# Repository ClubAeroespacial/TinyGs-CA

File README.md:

# Placa ESP32-C3 + SX1278 (LoRa 433 MHz) — Version2

Bring-up y validación de la revisión **Version2** de la placa.
Módulos: **ESP32-C3-WROOM-02-N4** (4 MB) + módulo **SX1278** de 433 MHz con conector u.FL.

**Estado: hardware validado.** 5 unidades fabricadas (3 + 2), todas funcionando.
Enlace LoRa bidireccional confirmado entre dos placas.

---

## Pinout

Verificado de dos formas independientes: extraído del netlist de KiCad
(`Version2.kicad_pcb`) y confirmado con firmware que corre en la placa.

| Señal | GPIO | Pad del módulo | Nota |
|---|---|---|---|
| LoRa SCK | **10** | 10 | |
| LoRa MISO | **6** | 5 | |
| LoRa MOSI | **7** | 6 | |
| LoRa NSS | **8** | 7 | strapping pin — ver ERRATA #4 |
| LoRa RESET | **5** | 4 | |
| LoRa DIO0 | **4** | 3 | conectado, permite usar interrupciones |
| UART TX | **21** | 12 | compartido con el LED — ver ERRATA #1 |
| UART RX | **20** | 11 | |
| Botón RESET | EN | 2 | |
| Botón BOOT | **0** | 18 | no es strapping pin — ver ERRATA #2 |
| Pull-up 10k (R10) | 2 | 16 | strapping, correcto |
| Pull-up 10k (R11) | 8 | 7 | strapping, correcto |

**GPIO libres:** 1, 3, 9, 18, 19
**DIO1–DIO5 del SX1278:** sin conectar

```cpp
#define PIN_SCK   10
#define PIN_MISO   6
#define PIN_MOSI   7
#define PIN_NSS    8
#define PIN_RST    5
#define PIN_DIO0   4
```

---

## Estado de validación

| Qué | Estado | Evidencia |
|---|---|---|
| Regulador 3.3 V (AMS1117) | OK | 3.3 V medidos, sin cortos |
| Arranque del ESP32-C3 | OK | mensaje de la ROM en UART |
| Flash 4 MB | OK | `flash-id` y sketches corriendo |
| UART bidireccional | OK | consola + flasheo exitoso |
| Modo programación | OK | `boot:0x5 (DOWNLOAD(USB/UART0/1))` |
| WiFi + estabilidad de fuente | OK | 6 redes, sin brownout en el pico de ~350 mA |
| SPI hacia el SX1278 | OK | `RegVersion = 0x12` estable |
| **Enlace LoRa bidireccional** | **OK** | PING/PONG entre 2 placas y test 14 del banco |
| **Test de producción completo** | **OK** | **14/14** en las unidades probadas |

Valores de referencia de placa sana: WiFi **-48 a -51 dBm** con 10-14 redes,
piso de ruido LoRa **-123 dBm**, frecuencia por defecto **434.0 MHz**.
Ver la tabla completa en [ERRATA.md](ERRATA.md).

### Todavía sin validar

- Alcance real (requiere antenas u.FL → SMA, aún no disponibles)
- Consumo en régimen y a batería
- Comportamiento térmico bajo carga sostenida

> **Nota sobre el -124 dBm:** la sensibilidad del SX1278 en SF7/BW125 es -123 dBm.
> El enlace funcionó **en el límite físico del chip**, sin antena y a 2 dBm, con
> ~8% de paquetes exitosos. Eso no es una falla: es el resultado esperado con los
> conectores u.FL al aire. Con antenas se espera -40 a -50 dBm a corta distancia.

---

## Cómo flashear

El programador usado es un **PL2303 sin DTR/RTS**, así que el modo descarga se
entra a mano.

### Cableado (TX y RX van cruzados)

```
PL2303              J2
------              --------------
GND     --------->  GND   (pin 1)
+5V     --------->  5V    (pin 2)
RXD     <---------  TX    (pin 3)
TXD     --------->  RX    (pin 4)
(nada)              RST   (pin 5)
(nada)              DTR   (pin 6)
```

### Configuración de Arduino IDE

| Opción | Valor |
|---|---|
| Board | ESP32C3 Dev Module |
| **USB CDC On Boot** | **Disabled** |
| Flash Mode | DIO |
| Flash Size | 4MB (32Mb) |
| Upload Speed | 921600 (probado y estable) |

### Secuencia

```
1. Mantener BOOT apretado
2. Apretar y soltar RESET
3. Soltar BOOT
4. Verificar en el monitor: boot:0x... (DOWNLOAD(USB/UART0/1))
5. Cerrar el Monitor Serie
6. Upload
7. Apretar RESET a mano (no hay RTS conectado)
```

**Indicador infalible:** el `boot:0x...` del mensaje de arranque.
`DOWNLOAD` = listo para flashear. `SPI_FAST_FLASH_BOOT` = no entraste.

---

## Sketches

| Carpeta | Qué prueba | Cuándo usarlo |
|---|---|---|
| `00_test_produccion/` | **14 pruebas automáticas con veredicto APROBADA / RECHAZADA** y línea CSV para planilla | **El de todos los días.** Es el banco de pruebas del lote. Ver la calibración de umbrales en ERRATA.md antes de correr una tanda |
| `04_test_lucas/` | Lee `RegVersion` del SX1278 por SPI | Primer test de una placa nueva si querés algo mínimo. 70 líneas, sin librerías |
| `01_smoke_test/` | CPU, flash, UART, LED, escaneo de WiFi | Validación general. El escaneo de WiFi es el que fuerza el pico de 350 mA y detecta problemas de fuente |
| `05_buscar_led/` | Versión corta del anterior | Cuando solo querés el estrés de fuente sin todo lo demás |
| `02_scan_sx1278/` | Encuentra los pines SPI por fuerza bruta | Si alguna vez hay una revisión nueva y no se conoce el pinout. Con el comando `v` verifica un pinout conocido en 2 segundos |
| `03_lora_pingpong/` | **Enlace de radio real entre 2 placas** | El único test que valida el amplificador, el cristal y el camino de antena |

> `04_test_lucas.ino` está **sin modificar**, tal como fue escrito originalmente.
> Se conserva así a propósito: es la referencia contra la que se comparó todo lo demás.

### Ping-pong: cómo se corre

El **mismo sketch** va en las dos placas. Las dos arrancan como RESPONDEDOR.
En la que tiene consola se manda `a` y pasa a EMISOR.

```
a  -> pasar a EMISOR        s  -> estadísticas
b  -> pasar a RESPONDEDOR   r  -> medir piso de ruido
t<n> -> potencia TX (2-17)  f<n> -> spreading factor (7-12)
d  -> cazar el pin DIO0
```

**Sin antena: 2 dBm y las placas a 5-10 cm.** No subir la potencia: el PA se
degrada transmitiendo contra un circuito abierto, y la degradación es silenciosa.

---

## Documentos

- **[ERRATA.md](ERRATA.md)** — los 7 defectos encontrados y qué cambiar en la v2
- **[00_GUIA_BRINGUP.md](00_GUIA_BRINGUP.md)** — guía completa de bring-up con mediciones
- **[PASOS_TEST_LUCAS.md](PASOS_TEST_LUCAS.md)** — procedimiento paso a paso con hitos

---

## Pendientes

- [ ] Comprar pigtails u.FL → SMA y antenas de 433 MHz (×5)
- [ ] Medir alcance real al aire libre
- [ ] Adaptador USB-TTL con DTR/RTS (CP2102 o CH340) para reset automático
- [ ] Regenerar los gerbers desde Version2 — ver ERRATA #7
- [ ] Aplicar los cambios de ERRATA.md a la v3

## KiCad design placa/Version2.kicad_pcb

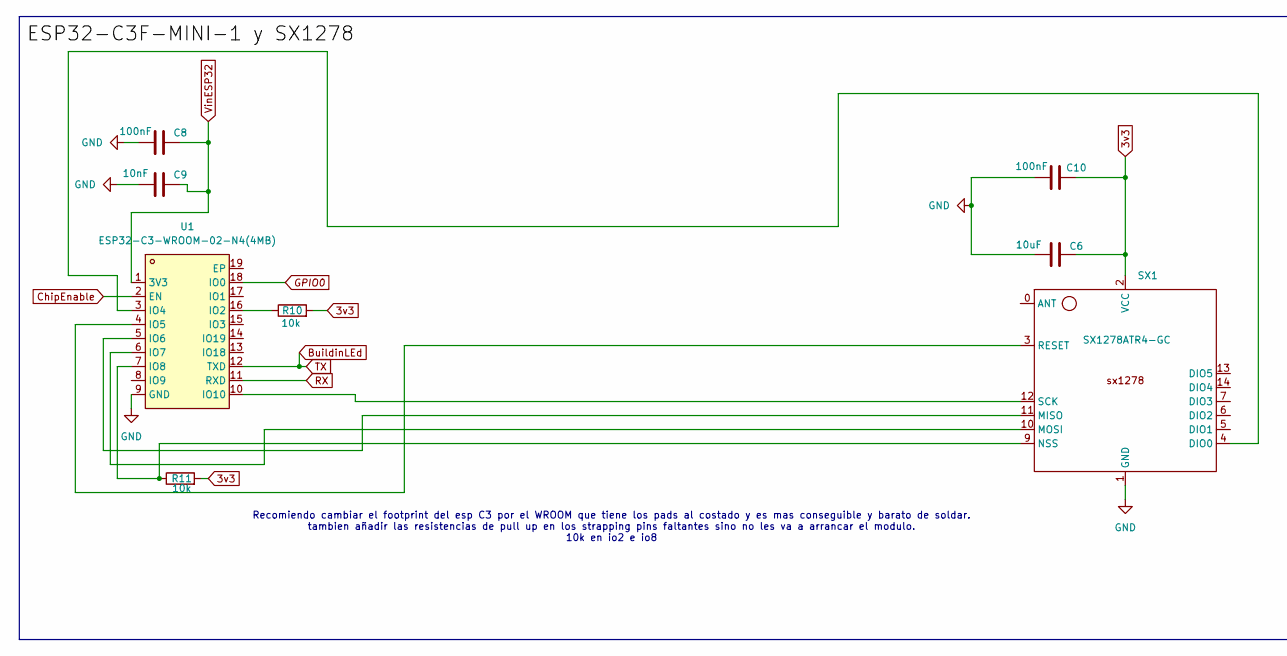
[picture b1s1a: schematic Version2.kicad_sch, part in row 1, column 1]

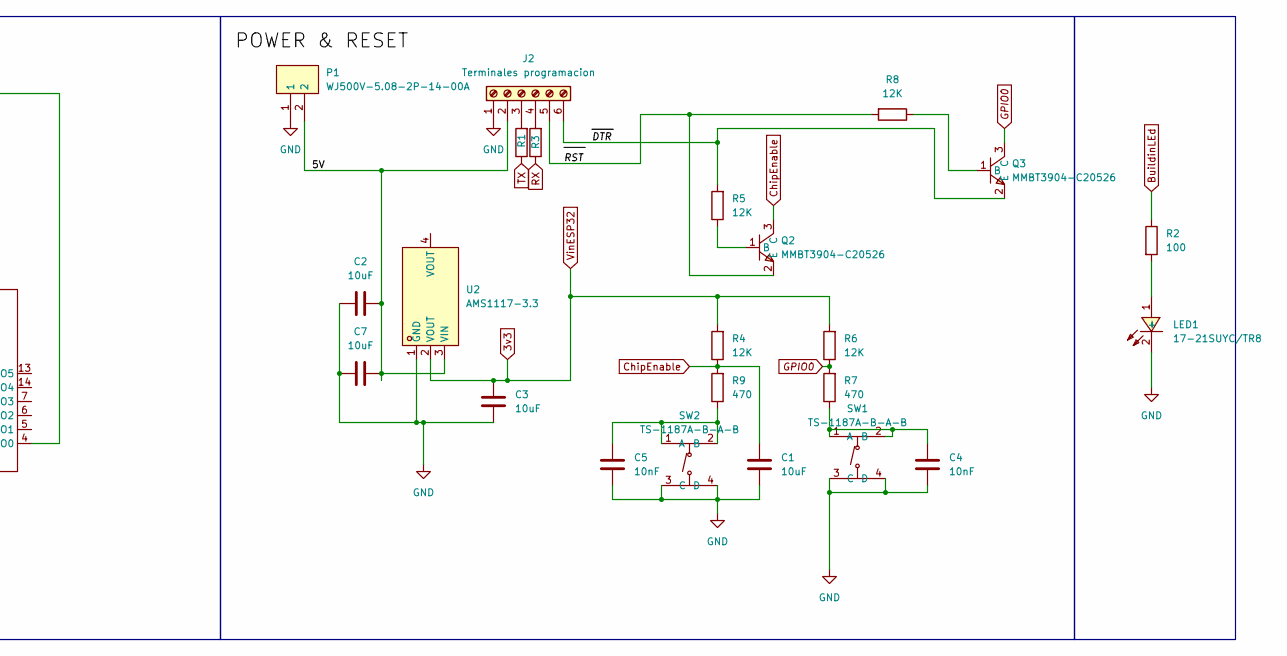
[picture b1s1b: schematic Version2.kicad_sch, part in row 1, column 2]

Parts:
C1, C2, C3, C6, C7: 10uF; C_0805_2012Metric
C4, C5, C9: 10nF; C_0402_1005Metric
C8, C10: 100nF; C_0402_1005Metric
J2: Terminales programacion; PinHeader_1x06_P2.54mm_Vertical; LCSC part C42431807
LED1: 17-21SUYC/TR8; LED_0805_2012Metric; LCSC Part C2296
P1: WJ500V-5.08-2P-14-00A; CONN-TH_2P-P5.00_WJ500V-5.08-2P; LCSC Part C8465
Q2, Q3: MMBT3904-C20526; SOT-23-3_L2.9-W1.3-P1.90-LS2.4-BR; LCSC Part C20526
R1, R3: 10; R_0603_1608Metric
R2: 100; R_0603_1608Metric
R4, R5, R6, R8: 12K; R_0603_1608Metric
R7, R9: 470; R_0603_1608Metric
R10, R11: 10k; R_0603_1608Metric; LCSC Part C31850
SW1, SW2: TS-1187A-B-A-B; SW-SMD_4P-L5.1-W5.1-P3.70-LS6.5-TL_H1.5; LCSC Part C318884
SX1: SX1278ATR4-GC; Sin título; LCSC part C42381680
U1: ESP32-C3-WROOM-02-N4(4MB); BULETM-SMD_ESPRESSIF_ESP32-C3-WROOM-02-N4-4MB; LCSC Part C2934560
U2: AMS1117-3.3; SOT-223-3_L6.5-W3.4-P2.30-LS7.0-BR; LCSC Part C6186

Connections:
3v3: C3.2, C6.2, C8.2, C9.2, C10.2, R4.2, R6.2, R10.2, R11.2, SX1.2 (VCC), U1.1 (3V3), U2.2 (VOUT)
/5V: C2.2, C7.2, J2.2, P1.2, U2.3 (VIN)
/DTR: J2.6, Q3.2 (E), R5.2
/RST: J2.5, Q2.2 (E), R8.2
BuildinLEd: R1.1, R2.1, U1.12 (TXD)
ChipEnable: C1.1, Q2.3 (C), R4.1, R9.2, U1.2 (EN)
GND: C1.2, C2.1, C3.1, C4.2, C5.2, C6.1, C7.1, C8.1, C9.1, C10.1, J2.1, LED1.2 (-), P1.1, SW1.3 (C), SW1.4 (D), SW2.3 (C), SW2.4 (D), SX1.1 (GND), U1.9 (GND), U2.1 (GND)
GPIO0: Q3.3 (C), R6.1, R7.2, U1.18 (IO0)
unnamed: J2.3, R1.2
unnamed: J2.4, R3.2
unnamed: LED1.1 (+), R2.2
unnamed: Q2.1 (B), R5.1
unnamed: Q3.1 (B), R8.1
unnamed: C4.1, R7.1, SW1.1 (A), SW1.2 (B)
unnamed: C5.1, R9.1, SW2.1 (A), SW2.2 (B)
unnamed: SX1.4 (DIO0), U1.3 (IO4)
unnamed: SX1.11 (MISO), U1.5 (IO6)
unnamed: SX1.10 (MOSI), U1.6 (IO7)
unnamed: R11.1, SX1.9 (NSS), U1.7 (IO8)
unnamed: SX1.3 (RESET), U1.4 (IO5)
unnamed: SX1.12 (SCK), U1.10 (IO10)
unnamed: R10.1, U1.16 (IO2)
RX: R3.1, U1.11 (RXD)

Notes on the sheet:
Recomiendo cambiar el footprint del esp C3 por el WROOM que tiene los pads al costado y es mas conseguible y barato de soldar. tambien añadir las resistencias de pull up en los strapping pins faltantes sino no les va a arrancar el modulo. 10k en io2 e io8

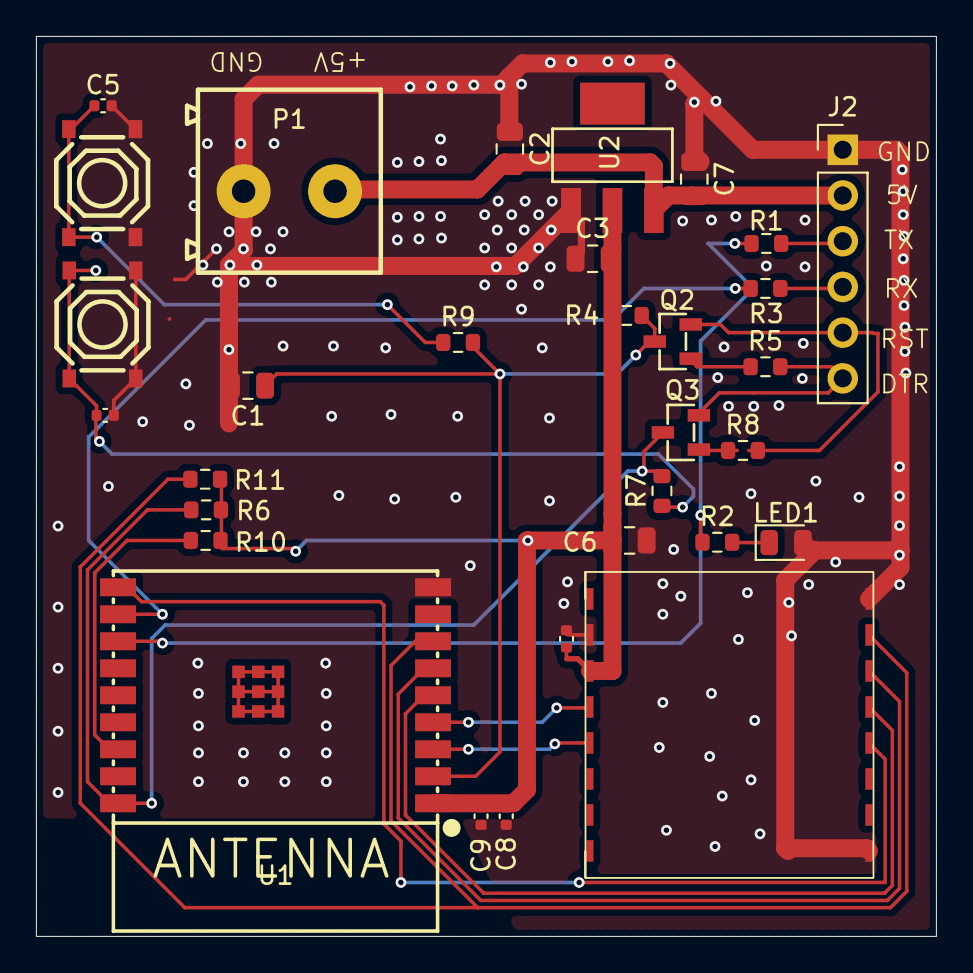
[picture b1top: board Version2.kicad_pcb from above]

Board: 2 copper layers, 50.0 x 50.0 mm, 31 parts (0 on the bottom side), 23 nets.

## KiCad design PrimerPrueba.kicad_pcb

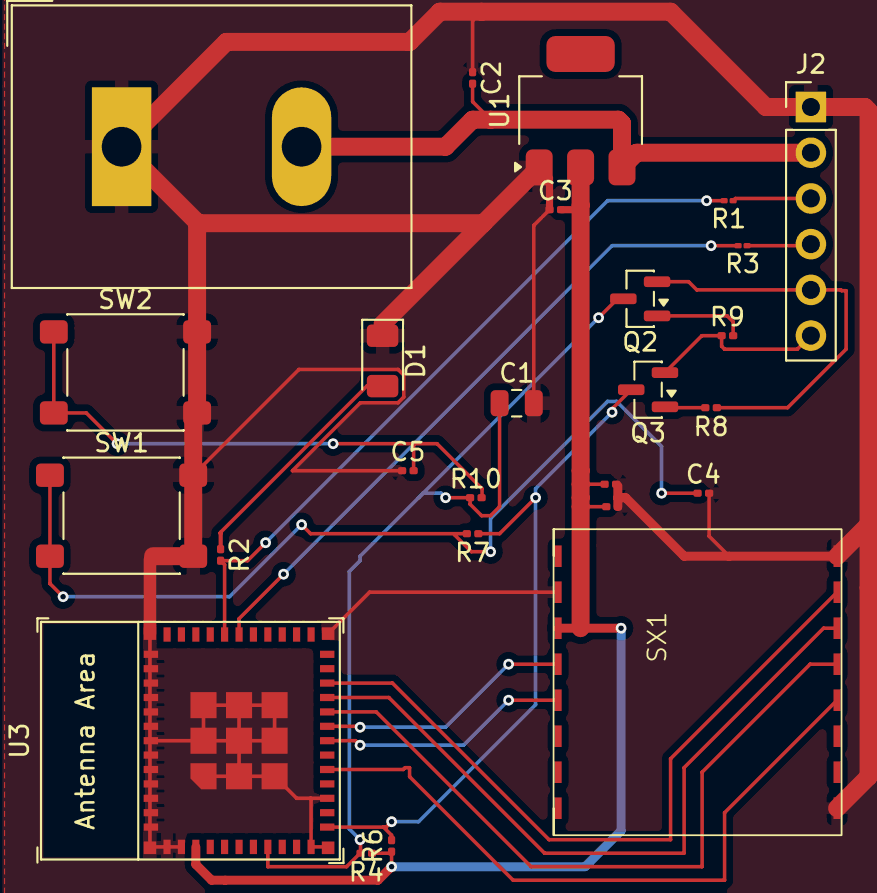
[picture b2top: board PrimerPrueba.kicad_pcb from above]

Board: 2 copper layers, 26 parts (0 on the bottom side), 22 nets.

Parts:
C1: CL21A226MPQNNNE; C_0805_2012Metric
C2, C3, C6: 10uF -CL10A106KP8NNNC; C_0201_0603Metric
C4, C5, C7: CC0603KRX7R9BB103; C_0201_0603Metric
D1: YLED1206R; LED_1206_3216Metric
J1: WJ500V-5.08-2P; TerminalBlock_Dinkle_DT-55-B01X-02_P10.00mm
J2: PH2.54-06PB2G-H25; PinHeader_1x06_P2.54mm_Vertical
Q2, Q3: BC817; SOT-23
R1, R3: GiantOhm GR0402J18RTAG00; R_01005_0402Metric
R2: RTT0360R0FTP; R_0201_0603Metric
R4, R6: RC0603FR-0712KL; R_0201_0603Metric
R7, R10: RC0603FR-07470RL; R_0201_0603Metric
R8, R9: RC0603FR-0712KL; C_0201_0603Metric
SW1, SW2: HX-6x6x7.3-TP FT square BUTTON; SW_SPST_PTS645Sx43SMTR92
SX1: SX1278ATR4-GC; Sin título
U1: LM1117S-3.3; SOT-223
U3: ESP32-C3-MINI-1

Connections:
3v3: C3.2, C6.1, C7.1, R4.1, R6.1, SX1.2 (VCC), U1.2 (VO), U3.3 (3V3)
/5V: C2.2, J1.2, J2.2, U1.3 (VI)
/DTR: J2.6, Q3.2 (E), R9.1
/RST: J2.5, Q2.2 (E), R8.1
BuildinLEd: R1.2, R2.2, U3.31 (GPIO21/U0TXD)
ChipEnable: C1.1, Q2.3 (C), R4.2, R10.1, U3.8 (EN/CHIP_PU)
GND: C1.2, C2.1, C3.1, C4.2, C5.1, C6.2, C7.2, D1.1 (K), J1.1, J2.1, SW1.1 (A), SW1.2 (A), SW2.1 (A), SX1.1 (GND), U1.1 (GND), U3.1 (GND), U3.2 (GND), U3.11 (GND), U3.14 (GND), U3.36 (GND), U3.37 (GND), U3.38 (GND), U3.39 (GND), U3.40 (GND), U3.41 (GND), U3.42 (GND), U3.43 (GND), U3.44 (GND), U3.45 (GND), U3.46 (GND), U3.47 (GND), U3.48 (GND), U3.49 (GND), U3.50 (GND), U3.51 (GND), U3.52 (GND), U3.53 (GND)
GPIO0: Q3.3 (C), R6.2, R7.1, U3.12 (GPIO0/ADC1_CH0/XTAL_32K_P)
unnamed: C4.1, R7.2, SW1.2 (A), SW1.sw1r7
unnamed: C5.2, R10.2, SW2.2 (A), SW2.sw2
unnamed: D1.2 (A), R2.1
unnamed: J2.3, R1.1
unnamed: J2.4, R3.1
unnamed: Q2.1 (B), R9.2
unnamed: Q3.1 (B), R8.2
unnamed: SX1.4 (DIO0), U3.18 (GPIO4/ADC1_CH4)
unnamed: SX1.11 (MISO), U3.20 (GPIO6)
unnamed: SX1.10 (MOSI), U3.21 (GPIO7)
unnamed: SX1.9 (NSS), U3.22 (GPIO8)
unnamed: SX1.3 (RESET), U3.19 (GPIO5/ADC2_CH0)
unnamed: SX1.12 (SCK), U3.16 (GPIO10)
RX: R3.2, U3.30 (GPIO20/U0RXD)

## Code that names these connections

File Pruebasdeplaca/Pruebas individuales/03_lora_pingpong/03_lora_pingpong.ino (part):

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#define PIN_SCK     10
#define PIN_MISO    6
#define PIN_MOSI    7
#define PIN_NSS     8      // OJO: GPIO8 es strapping pin. Ver nota abajo.
#define PIN_RST     5
#define PIN_DIO0    4      // CONFIRMADO en el netlist de KiCad (SX1.DIO0 -> U1 IO4)

// EL LED NO SE PUEDE USAR. Esta cableado a GPIO21, que es el TX del UART.
// Como el TX reposa en alto, el LED esta PRENDIDO FIJO siempre y titila cuando
// sale data serie. No hay forma de controlarlo sin romper la consola.
#define PIN_LED     -1     // dejalo en -1. No lo cambies.
// ############################################################################
//
// NOTA SOBRE GPIO8 = NSS
// GPIO8 es un strapping pin del ESP32-C3: tiene que estar en ALTO al soltar el
// reset o el chip no arranca. Funciona porque:
//   - NSS reposa en alto (que es justo lo que GPIO8 necesita)
//   - R11 (10k a 3V3) lo mantiene arriba antes de que el ESP32 lo maneje
// Pero es fragil: cualquier cosa que tire GPIO8 a masa durante el reset deja la
// placa sin arrancar. GPIO4 y GPIO9 estan libres. Para la v2, move NSS a GPIO4.
//
// ############################################################################

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    Serial.println(F("  Cargalo en PIN_DIO0 arriba y confirmalo contra el esquematico."));
  } else {
    Serial.println(F("  Varios pines en alto. Algunos tienen pull-up (GPIO2 con R10,"));
    Serial.println(F("  GPIO9 interno, GPIO0 con R6): esos son falsos positivos, siempre"));
    Serial.println(F("  estan altos. El que te interesa es uno que NO tenga pull-up."));
    Serial.println(F("  La forma definitiva de saberlo sigue siendo el esquematico."));
  }
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
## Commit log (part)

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2026-05-06 Primera prueba de la PCB
2026-05-06 Id de los componentes listo
2026-05-06 botones agregados
2026-05-30 correctiones con codigo de componente
